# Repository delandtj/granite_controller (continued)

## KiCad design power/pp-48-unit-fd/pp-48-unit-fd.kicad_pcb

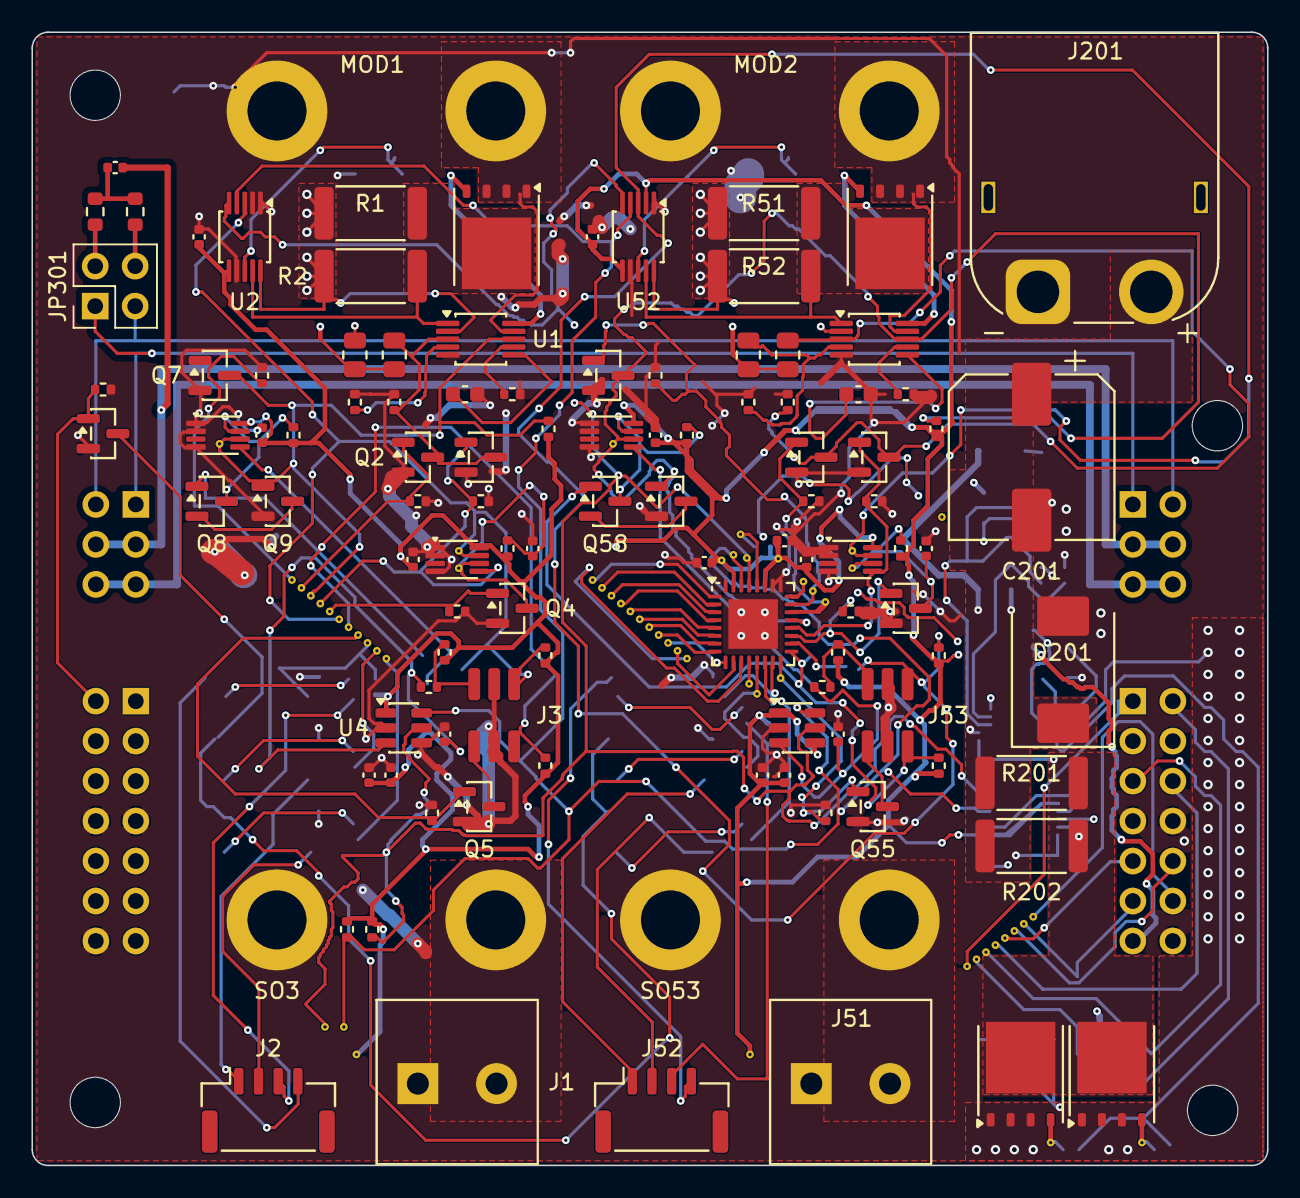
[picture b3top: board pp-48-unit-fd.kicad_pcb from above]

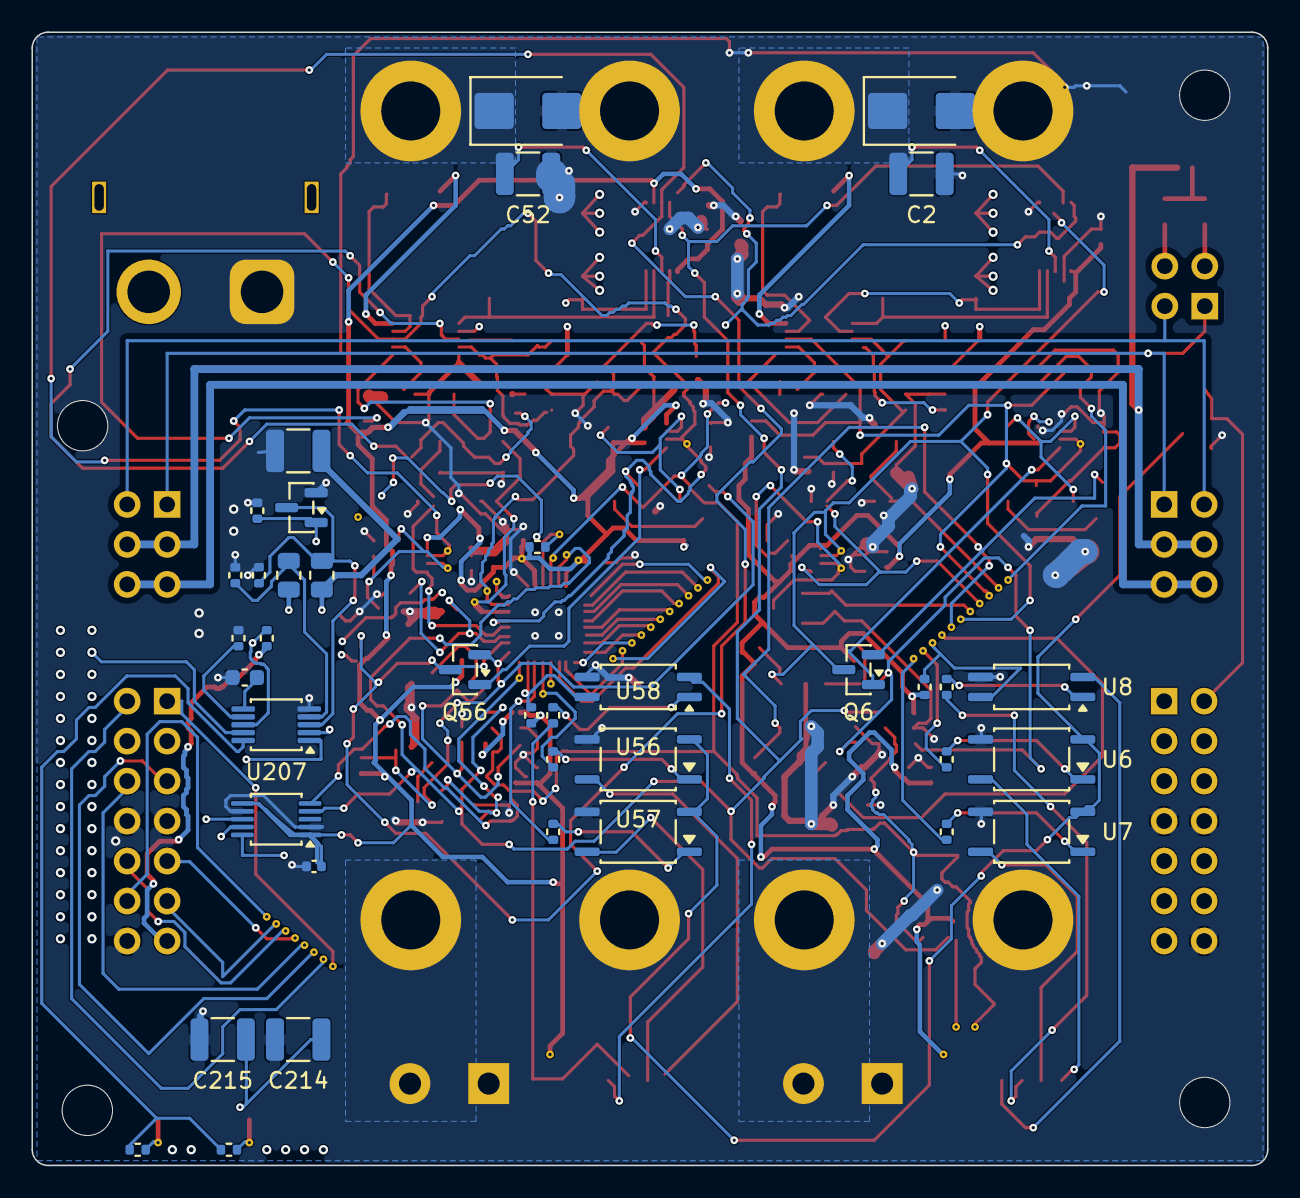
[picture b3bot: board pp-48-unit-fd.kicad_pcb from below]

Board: 4 copper layers, 78.5 x 72.0 mm, 214 parts (42 on the bottom side), 98 nets.

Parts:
BV100, BV101, BV102, BV103, BV104, BV105, BV106, BV107, BV108, BV109, BV110, BV150, BV151, BV152, BV153, BV154, BV155, BV156, BV157, BV158, BV159, BV160, BV900, BV901, BV902, BV903, BV904, BV905, BV906, BV907: (no value)
C1, C51: 100n; C_0603_1608Metric
C2, C52, C202, C214, C215: 2.2u 100V; C_1210_3225Metric
C3, C4, C5, C6, C9, C10, C12, C13, C53, C54, C55, C56, C60, C62, C216: 100n; C_0402_1005Metric
C11, C61: 1u; C_0402_1005Metric
C201: 47u 100V; CP_Elec_10x10
C203: 220n; C_0603_1608Metric
C301: 4.7n; C_0402_1005Metric
D1, D51: SMBJ60A; D_SMB
D201: SMDJ60A; D_SMC
EV12, EV13, EV16, EV22, EV23, EV24, EV29, EV30: (no value)
GV202, GV203: (no value)
H1, H2, H3, H4: MountingHole_3.2mm_M3
J1, J51: NODE 19V; TerminalBlock_Degson_DG128-5.0-02P
J2, J52: FRONT PANEL; JST_GH_SM04B-GHS-TB_1x04-1MP_P1.25mm_Horizontal
J3, J53: AUX; PM_Aux_Socket_2x03_P1.27
J201: XT60PW-M; AMASS_XT60PW-M_1x02_P7.20mm_Horizontal
J301: CHAIN IN; PinHeader_2x07_P2.54mm_Horizontal
J302: CHAIN OUT; PinSocket_2x07_P2.54mm_Horizontal
J303: LINK IN; PinHeader_2x03_P2.54mm_Horizontal
J304: LINK OUT; PinSocket_2x03_P2.54mm_Horizontal
JP301: TERM; PinHeader_2x02_P2.54mm_Vertical
MOD1, MOD2: PM_Module_Outline
PV1B3, PV1B4, PV3A, PV3B: (no value)
Q1, Q51: CSD19532Q5B; TDSON-8-1
Q2, Q3, Q4, Q5, Q6, Q7, Q8, Q9, Q10, Q52, Q53, Q54, Q55, Q56, Q57, Q58, Q59, Q204: 2N7002; SOT-23
Q202, Q203: BSC040N10NS5; TDSON-8-1
R1, R2, R51, R52: 7m 2W; R_2512_6332Metric
R3, R53, R233: 143k; R_0805_2012Metric
R4, R54, R234: 11k; R_0402_1005Metric
R5, R55, R235: 124k; R_0805_2012Metric
R6, R56, R236: 4.99k; R_0402_1005Metric
R7, R57: 13.7k; R_0402_1005Metric
R8, R13, R14, R15, R30, R58, R63, R64, R65, R238: 10k; R_0402_1005Metric
R9, R10, R11, R12, R23, R28, R29, R31, R59, R60, R61, R62, R73, R78, R79, R214: 100k; R_0402_1005Metric
R19, R20, R69, R70: 270; R_0402_1005Metric
R21, R71: 220; R_0402_1005Metric
R22, R72: 47k; R_0402_1005Metric
R24, R74: 1k; R_0402_1005Metric
R26, R27: 4.7k; R_0402_1005Metric
R201, R202: 6m 2W; R_2512_6332Metric
R210, R211: 10; R_0402_1005Metric
R237: 20.0k; R_0402_1005Metric
R301, R302: 60.4; R_0603_1608Metric
RV1: (no value)
SO1, SO51: S1 VIN; PM_Standoff_M2x7_SMTSO
SO2, SO52: S2 GND; PM_Standoff_M2x7_SMTSO
SO3, SO53: S3 GND; PM_Standoff_M2x7_SMTSO
SO4, SO54: S4 VOUT; PM_Standoff_M2x7_SMTSO
SV8, SV9: (no value)
U1, U51, U207: LM5069MM-2; MSOP-10_3x3mm_P0.5mm
U2, U52, U208: INA228AIDGSR; TSSOP-10_3x3mm_P0.5mm
U3, U10, U53, U60: 74LVC1G74; VSSOP-8_2.3x2mm_P0.5mm
U4, U54: ADC121C027CIMK; TSOT-23-6
U5: TCA6424ARGJR; VQFN-32-1EP_5x5mm_P0.5mm_EP3.15x3.15mm
U6, U7, U56, U57: TLP176AM; SOIC-4_4.55x3.7mm_P2.54mm
U8, U58: TLP291; SOIC-4_4.55x2.6mm_P1.27mm
UV1: (no value)
XV1A1, XV1A2, XV1A3, XV1B1, XV1B2, XV1B3: (no value)

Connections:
+3V3: C3.1, C4.1, C9.1, C10.1, C11.1, C12.1, C13.1, C53.1, C54.1, C60.1, C61.1, C62.1, C216.1, J301.13, J302.13, PV1B3.1, PV1B4.1, PV3A.1, PV3B.1, R8.1, R11.1, R13.1, R14.1, R15.1, R22.1, R26.1, R27.1, R28.1, R30.2, R58.1, R61.1, R63.1, R64.1, R65.1, R72.1, R78.1, R238.1, U2.6, U3.8, U4.1, U5.27, U5.31, U10.8, U52.2, U52.6, U53.8, U54.1, U54.4, U60.8, U208.1, U208.6
/Chain/AUX_12V: J303.5, J303.6, J304.5, J304.6
/Chain/CAN_N: J303.2, J304.2, JP301.3
/Chain/CAN_P: J303.1, J304.1, JP301.1
/Chain/CH1_SCL: BV907.1, J301.10, J302.12
/Chain/CH1_SDA: BV906.1, J301.9, J302.11
/Chain/CH2_SCL: BV905.1, J301.6, J302.10
/Chain/CH2_SDA: BV904.1, J301.5, J302.9
/Chain/CH3_SCL: BV903.1, J301.4, J302.6
/Chain/CH3_SDA: BV902.1, J301.3, J302.5
/Chain/LINK_GND: C301.2, J303.3, J303.4, J304.3, J304.4
/Chain/TERM_H: JP301.2, R301.1
/Chain/TERM_L: JP301.4, R302.2
/Chain/TERM_MID: C301.1, R301.2, R302.1
/EXP_RSTN: BV900.1, J301.1, J302.1, R30.1, RV1.1, U5.28
/Input/GATE: R210.1, R211.2, U207.10
/Input/OVLO: R235.2, R236.1, U207.4
/Input/PWR: R237.1, U207.7
/Input/TIMER: C203.1, U207.6
/Input/USENSE: Q202.5, Q203.5, R201.2, R202.2, U207.1, U208.9
/Input/UVLO: Q204.3, R233.2, R234.1, U207.3
/PRESS_EN: BV901.1, J301.2, J302.2, Q10.1, R31.1
/SEG_SCL: EV29.1, J301.12, R27.2, SV9.1, U2.5, U4.5, U5.29, U52.5, U54.5, U208.5
/SEG_SDA: EV30.1, J301.11, R26.2, SV8.1, U2.4, U4.6, U5.30, U52.4, U54.6, U208.4
/U_OFF: EV12.1, Q204.1, R214.1, U5.12, UV1.1
/U_PGD: EV24.1, R238.2, U5.24, U207.8
/Unit/A_ARM: Q6.1, U10.5
/Unit/A_ARMS_M: Q8.2, Q9.3
/Unit/A_ARMS_N: Q8.3, R28.2, U10.7
/Unit/A_CLRN: C5.1, Q4.3, R11.2, U3.6, XV1A2.1
/Unit/A_DISARM: BV100.1, BV150.1, Q7.1, R29.1, U5.1
/Unit/A_GATE: Q1.4, U1.10
/Unit/A_ID: J3.3, R15.2, R24.2
/Unit/A_ID_F: C6.1, R24.1, U4.3
/Unit/A_LCLR: BV104.1, BV154.1, Q4.1, R12.1, U5.5
/Unit/A_LED: BV108.1, BV158.1, R22.2, U5.9, U8.4
/Unit/A_LQ: BV103.1, BV153.1, Q3.1, R10.1, U3.5, U5.4
/Unit/A_NODE: J1.2, SO4.1
/Unit/A_OFF: BV101.1, BV151.1, Q2.1, R9.1, U5.2
/Unit/A_OUT: C2.1, D1.1, Q1.1, Q1.2, Q1.3, SO1.1, U1.9, U2.8
/Unit/A_OVK: BV105.1, BV155.1, J3.1, Q6.3, R13.2, U2.3, U3.7, U5.6, XV1A1.1
/Unit/A_OVLO: R5.2, R6.1, U1.4
/Unit/A_PG: BV106.1, BV156.1, J3.2, Q6.2, Q8.1, R14.2, U5.7
/Unit/A_PGD: BV102.1, BV152.1, Q7.3, Q9.1, R8.2, U1.8, U5.3, U10.6, XV1A3.1
/Unit/A_PLED_A: R21.2, U8.1
/Unit/A_PLED_N: J2.4, U8.2
/Unit/A_PLED_P: J2.3, R21.1
/Unit/A_PWR: R7.1, U1.7
/Unit/A_PWRD: BV109.1, BV159.1, R19.1, U5.10
/Unit/A_PWRD_A: R19.2, U6.1
/Unit/A_PWR_SW: J2.1, U6.6
/Unit/A_RSTD: BV110.1, BV160.1, R20.1, U5.11
/Unit/A_RSTD_A: R20.2, U7.1
/Unit/A_RST_SW: J2.2, U7.6
/Unit/A_RUN: J3.4, Q5.3
/Unit/A_RUNOFF: BV107.1, BV157.1, Q5.1, R23.1, U5.8
/Unit/A_SENSE: Q1.5, R1.2, R2.2, U1.1, U2.9
/Unit/A_TIMER: C1.1, U1.6
/Unit/A_UVLO: Q2.3, Q3.3, R3.2, R4.1, U1.3
/Unit/B_ARM: Q56.1, U60.5
/Unit/B_ARMS_M: Q58.2, Q59.3
/Unit/B_ARMS_N: Q58.3, R78.2, U60.7
/Unit/B_CLRN: C55.1, Q54.3, R61.2, U53.6, XV1B2.1
/Unit/B_DISARM: EV23.1, Q57.1, R79.1, U5.23
/Unit/B_GATE: Q51.4, U51.10
/Unit/B_ID: J53.3, R65.2, R74.2
/Unit/B_ID_F: C56.1, R74.1, U54.3
/Unit/B_LCLR: Q54.1, R62.1, U5.19
/Unit/B_LED: R72.2, U5.15, U58.4
/Unit/B_LQ: Q53.1, R60.1, U5.20, U53.5
/Unit/B_NODE: J51.2, SO54.1
/Unit/B_OFF: EV22.1, Q52.1, R59.1, U5.22
/Unit/B_OUT: C52.1, D51.1, Q51.1, Q51.2, Q51.3, SO51.1, U51.9, U52.8
/Unit/B_OVK: J53.1, Q56.3, R63.2, U5.18, U52.3, U53.7, XV1B1.1
/Unit/B_OVLO: R55.2, R56.1, U51.4
/Unit/B_PG: J53.2, Q56.2, Q58.1, R64.2, U5.17
/Unit/B_PGD: Q57.3, Q59.1, R58.2, U5.21, U51.8, U60.6, XV1B3.1
/Unit/B_PLED_A: R71.2, U58.1
/Unit/B_PLED_N: J52.4, U58.2
/Unit/B_PLED_P: J52.3, R71.1
/Unit/B_PWR: R57.1, U51.7
/Unit/B_PWRD: EV13.1, R69.1, U5.13
/Unit/B_PWRD_A: R69.2, U56.1
/Unit/B_PWR_SW: J52.1, U56.6
/Unit/B_RSTD: R70.1, U5.14
/Unit/B_RSTD_A: R70.2, U57.1
/Unit/B_RST_SW: J52.2, U57.6
/Unit/B_RUN: J53.4, Q55.3
/Unit/B_RUNOFF: EV16.1, Q55.1, R73.1, U5.16
/Unit/B_SENSE: Q51.5, R51.2, R52.2, U51.1, U52.9
/Unit/B_TIMER: C51.1, U51.6
/Unit/B_UVLO: Q52.3, Q53.3, R53.2, R54.1, U51.3
/Unit/PRESS_RTN: Q10.3, U6.3, U7.3, U56.3, U57.3
GND: C1.2, C2.2, C3.2, C4.2, C5.2, C6.2, C9.2, C10.2, C11.2, C12.2, C13.2, C51.2, C52.2, C53.2, C54.2, C55.2, C56.2, C60.2, C61.2, C62.2, C201.2, C202.2, C203.2, C214.2, C215.2, C216.2, D1.2, D51.2, D201.2, J1.1, J3.5, J3.6, J51.1, J53.5, J53.6, J201.1, J301.7, J301.8, J301.14, J302.7, J302.8, J302.14, Q2.2, Q3.2, Q4.2, Q5.2, Q7.2, Q9.2, Q10.2, Q52.2, Q53.2, Q54.2, Q55.2, Q57.2, Q59.2, Q204.2, R4.2, R6.2, R7.2, R9.2, R10.2, R12.2, R23.2, R29.2, R31.2, R54.2, R56.2, R57.2, R59.2, R60.2, R62.2, R73.2, R79.2, R214.2, R234.2, R236.2, R237.2, SO2.1, SO3.1, SO52.1, SO53.1, U1.5, U2.1, U2.2, U2.7, U3.1, U3.2, U3.4, U4.2, U4.4, U5.25, U5.26, U5.33, U6.4, U7.4, U8.3, U10.1, U10.2, U10.4, U51.5, U52.1, U52.7, U53.1, U53.2, U53.4, U54.2, U56.4, U57.4, U58.3, U60.1, U60.2, U60.4, U207.5, U208.2, U208.7
unnamed: GV202.1, Q202.4, R210.2
unnamed: GV203.1, Q203.4, R211.1
VBUS: C214.1, C215.1, Q202.1, Q202.2, Q202.3, Q203.1, Q203.2, Q203.3, R1.1, R2.1, R3.1, R5.1, R51.1, R52.1, R53.1, R55.1, U1.2, U2.10, U51.2, U52.10, U207.9, U208.8
VIN: C201.1, C202.1, D201.1, J201.2, R201.1, R202.1, R233.1, R235.1, U207.2, U208.10

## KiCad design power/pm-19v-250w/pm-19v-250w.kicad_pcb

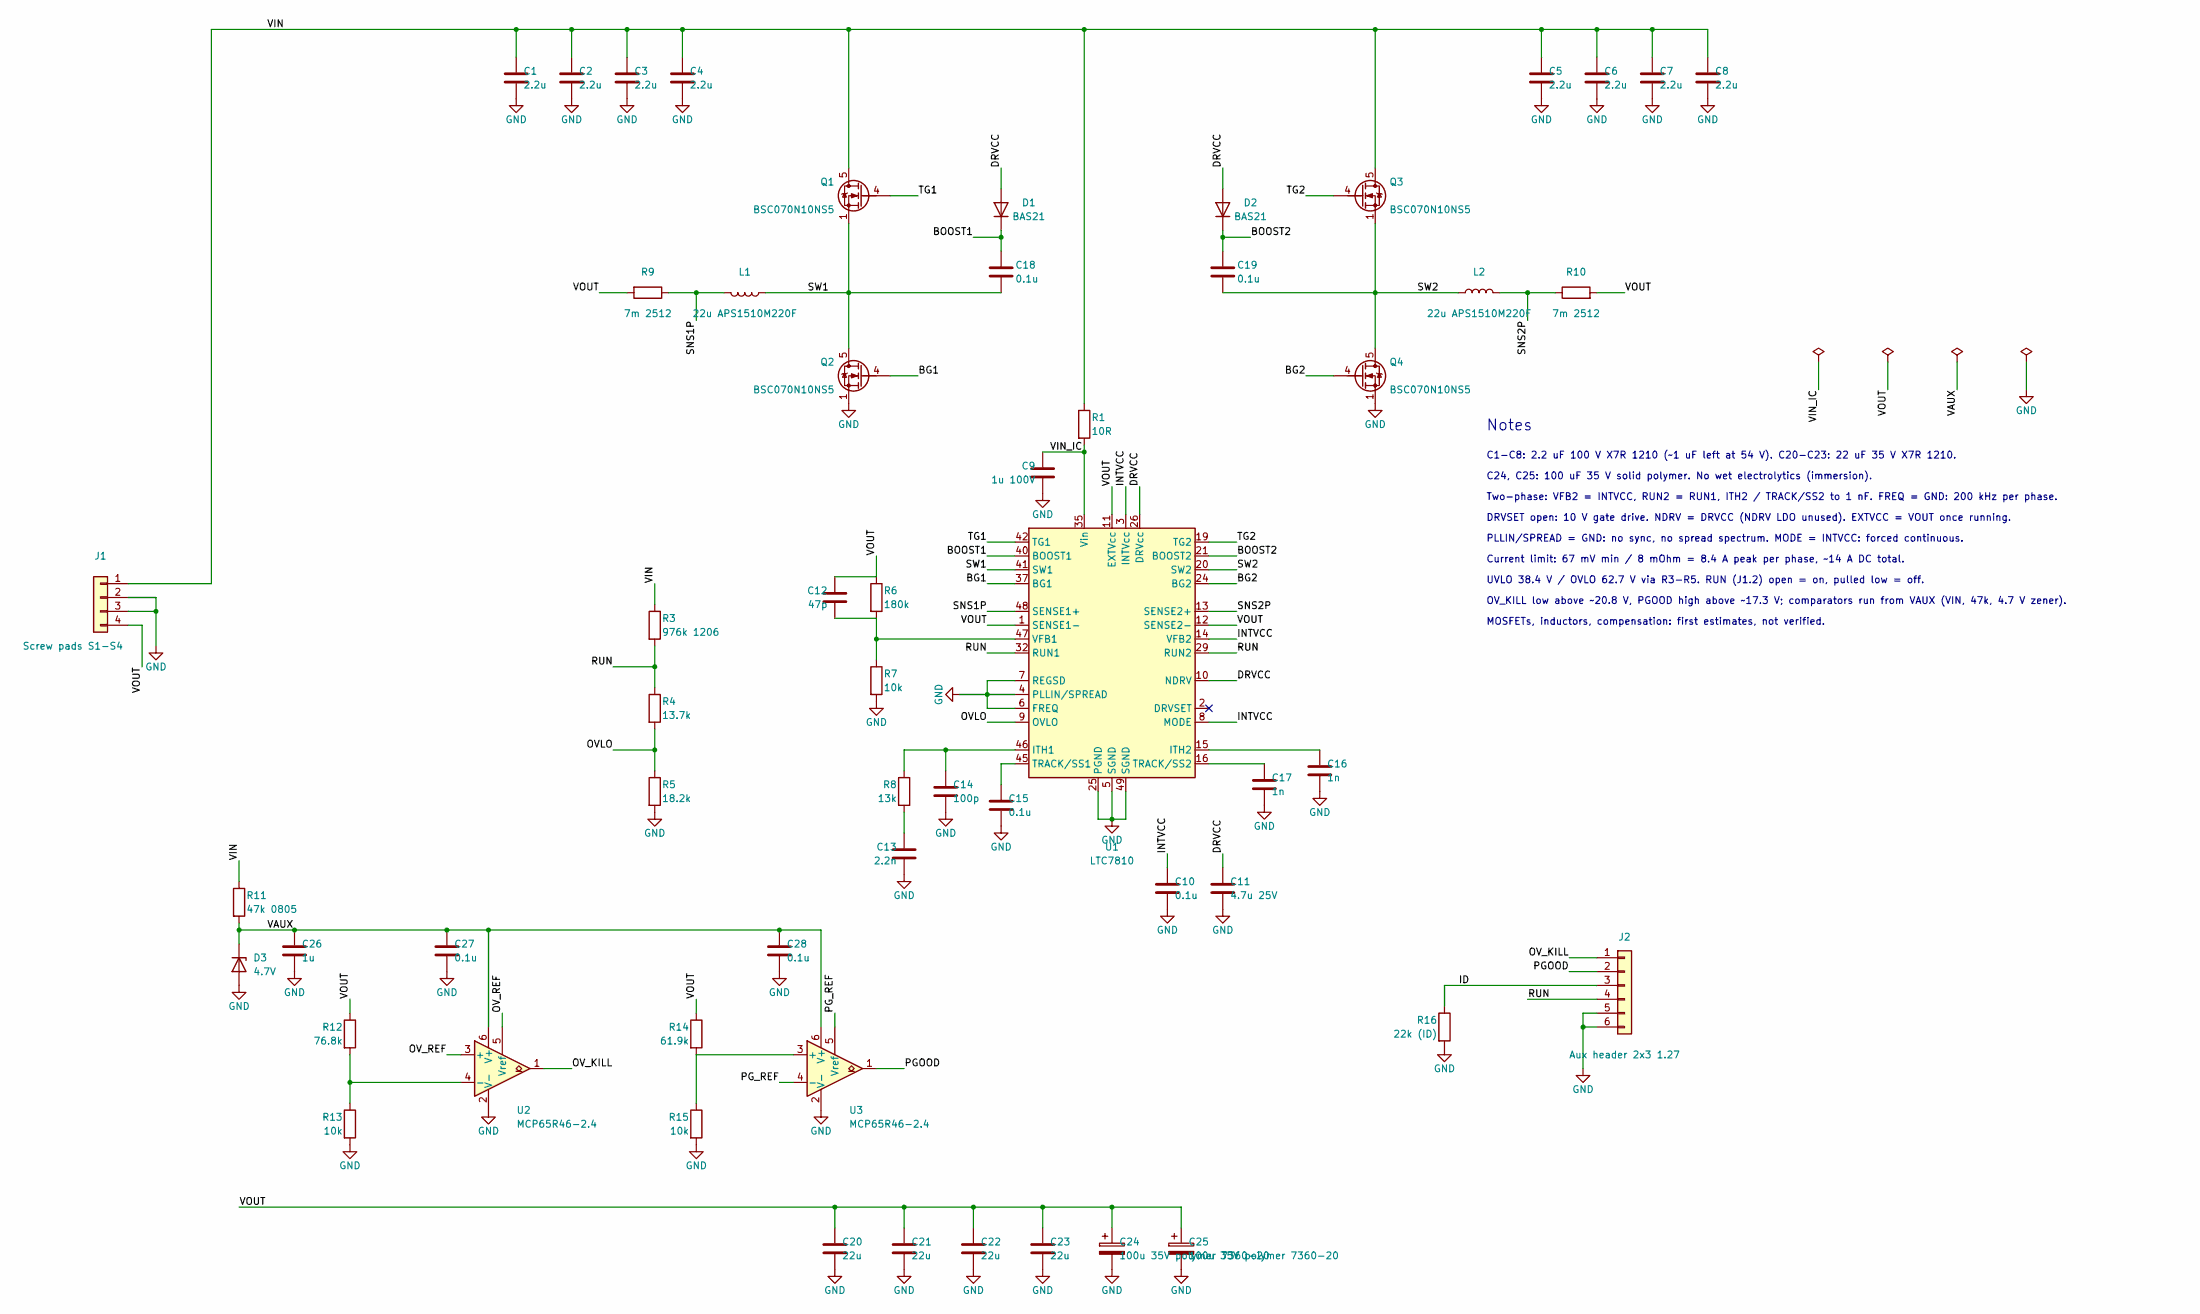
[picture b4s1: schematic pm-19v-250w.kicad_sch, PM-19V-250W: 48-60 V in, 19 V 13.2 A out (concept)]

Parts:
C1, C2, C3, C4, C5, C6, C7, C8: 2.2u; C_1210_3225Metric; LCSC C5449052
C9: 1u 100V; C_0805_2012Metric; LCSC C5370002
C10, C15, C18, C19, C27, C28: 0.1u; C_0402_1005Metric; LCSC C307331
C11: 4.7u 25V; C_0805_2012Metric; LCSC C354262
C12: 47p; C_0402_1005Metric; LCSC C1567
C13: 2.2n; C_0402_1005Metric; LCSC C2980802
C14: 100p; C_0402_1005Metric; LCSC C1546
C16, C17: 1n; C_0402_1005Metric; LCSC C1523
C20, C21, C22, C23: 22u; C_1210_3225Metric; LCSC C778721
C24, C25: 100u 35V polymer 7360-20; CP_EIA-7360-38_Kemet-E; LCSC C2158991
C26: 1u; C_0402_1005Metric; LCSC C52923
D1, D2: BAS21; D_SOD-323; LCSC C82466
D3: 4.7V; D_SOD-323; LCSC C107713
J1: Screw pads S1-S4; PM_Mount_M2
J2: Aux header 2x3 1.27; PM_Aux_Header_2x03_P1.27; LCSC C41376035
L1, L2: 22u APS1510M220F; L_Coilcraft_XAL1510-223; LCSC C49261404
Q1, Q2, Q3, Q4: BSC070N10NS5; TDSON-8-1; LCSC C534364
R1: 10R; R_0603_1608Metric; LCSC C22859
R3: 976k 1206; R_1206_3216Metric; LCSC C247164
R4: 13.7k; R_0603_1608Metric; LCSC C22793
R5: 18.2k; R_0402_1005Metric; LCSC C25859
R6: 180k; R_0402_1005Metric; LCSC C25760
R7, R13, R15: 10k; R_0402_1005Metric; LCSC C25744
R8: 13k; R_0402_1005Metric; LCSC C25754
R9, R10: 7m 2512; R_2512_6332Metric; LCSC C20608751
R11: 47k 0805; R_0805_2012Metric; LCSC C17713
R12: 76.8k; R_0402_1005Metric; LCSC C26987
R14: 61.9k; R_0402_1005Metric; LCSC C2933106
R16: 22k (ID); R_0603_1608Metric; LCSC C31850
U1: LTC7810; LQFP-48-1EP_7x7mm_P0.5mm_EP3.6x3.6mm; LCSC C581067
U2, U3: MCP65R46-2.4; SOT-23-6; LCSC C623510

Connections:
/BG1: Q2.4 (G), U1.37 (BG1)
/BG2: Q4.4 (G), U1.24 (BG2)
/BOOST1: C18.1, D1.1 (K), U1.40 (BOOST1)
/BOOST2: C19.1, D2.1 (K), U1.21 (BOOST2)
/DRVCC: C11.1, D1.2 (A), D2.2 (A), U1.10 (NDRV), U1.26 (DRVcc)
/ID: J2.3, R16.1
/INTVCC: C10.1, U1.3 (INTVcc), U1.8 (MODE), U1.14 (VFB2)
/OVLO: R4.2, R5.1, U1.9 (OVLO)
/OV_KILL: J2.1, U2.1
/OV_REF: U2.3 (+), U2.5 (Vref)
/PGOOD: J2.2, U3.1
/PG_REF: U3.4 (-), U3.5 (Vref)
/RUN: J2.4, R3.2, R4.1, U1.29 (RUN2), U1.32 (RUN1)
/SNS1P: L1.2, R9.1, U1.48 (SENSE1+)
/SNS2P: L2.2, R10.1, U1.13 (SENSE2+)
/SW1: C18.2, L1.1, Q1.1 (S), Q1.2 (S), Q1.3 (S), Q2.5 (D), U1.41 (SW1)
/SW2: C19.2, L2.1, Q3.1 (S), Q3.2 (S), Q3.3 (S), Q4.5 (D), U1.20 (SW2)
/TG1: Q1.4 (G), U1.42 (TG1)
/TG2: Q3.4 (G), U1.19 (TG2)
/VAUX: C26.1, C27.1, C28.1, D3.1 (K), R11.2, U2.6 (V+), U3.6 (V+)
/VIN: C1.1, C2.1, C3.1, C4.1, C5.1, C6.1, C7.1, C8.1, J1.1, Q1.5 (D), Q3.5 (D), R1.1, R3.1, R11.1
/VIN_IC: C9.1, R1.2, U1.35 (Vin)
/VOUT: C12.1, C20.1, C21.1, C22.1, C23.1, C24.1, C25.1, J1.4, R6.1, R9.2, R10.2, R12.1, R14.1, U1.1 (SENSE1-), U1.11 (EXTVcc), U1.12 (SENSE2-)
GND: C1.2, C2.2, C3.2, C4.2, C5.2, C6.2, C7.2, C8.2, C9.2, C10.2, C11.2, C13.2, C14.2, C15.2, C16.2, C17.2, C20.2, C21.2, C22.2, C23.2, C24.2, C25.2, C26.2, C27.2, C28.2, D3.2 (A), J1.2, J1.3, J2.5, J2.6, Q2.1 (S), Q2.2 (S), Q2.3 (S), Q4.1 (S), Q4.2 (S), Q4.3 (S), R5.2, R7.2, R13.2, R15.2, R16.2, U1.4 (PLLIN/SPREAD), U1.5 (SGND), U1.6 (FREQ), U1.7 (REGSD), U1.25 (PGND), U1.49 (SGND), U2.2 (V-), U3.2 (V-)
unnamed: C13.1, R8.2
unnamed: C14.1, R8.1, U1.46 (ITH1)
unnamed: C16.1, U1.15 (ITH2)
unnamed: C15.1, U1.45 (TRACK/SS1)
unnamed: C17.1, U1.16 (TRACK/SS2)
unnamed: C12.2, R6.2, R7.1, U1.47 (VFB1)
unnamed: R12.2, R13.1, U2.4 (-)
unnamed: R14.2, R15.1, U3.3 (+)

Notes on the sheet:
Notes
C1-C8: 2.2 uF 100 V X7R 1210 (~1 uF left at 54 V). C20-C23: 22 uF 35 V X7R 1210.
C24, C25: 100 uF 35 V solid polymer. No wet electrolytics (immersion).
Two-phase: VFB2 = INTVCC, RUN2 = RUN1, ITH2 / TRACK/SS2 to 1 nF. FREQ = GND: 200 kHz per phase.
DRVSET open: 10 V gate drive. NDRV = DRVCC (NDRV LDO unused). EXTVCC = VOUT once running.
PLLIN/SPREAD = GND: no sync, no spread spectrum. MODE = INTVCC: forced continuous.
Current limit: 67 mV min / 8 mOhm = 8.4 A peak per phase, ~14 A DC total.
UVLO 38.4 V / OVLO 62.7 V via R3-R5. RUN (J1.2) open = on, pulled low = off.
OV_KILL low above ~20.8 V, PGOOD high above ~17.3 V; comparators run from VAUX (VIN, 47k, 4.7 V zener).
MOSFETs, inductors, compensation: first estimates, not verified.

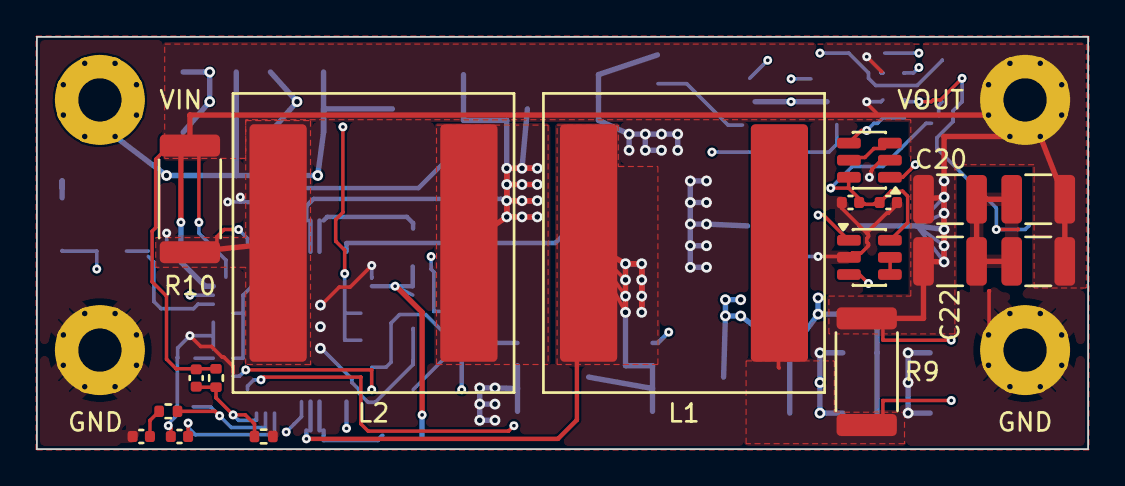
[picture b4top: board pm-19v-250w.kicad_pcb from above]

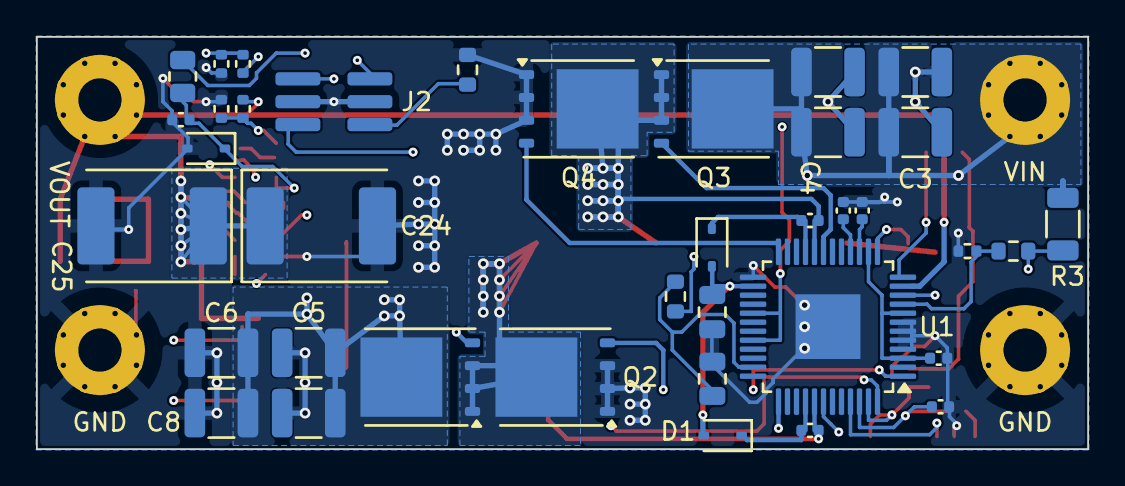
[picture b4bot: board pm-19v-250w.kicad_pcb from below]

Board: 4 copper layers, 58.4 x 22.9 mm, 57 parts (38 on the bottom side), 32 nets.

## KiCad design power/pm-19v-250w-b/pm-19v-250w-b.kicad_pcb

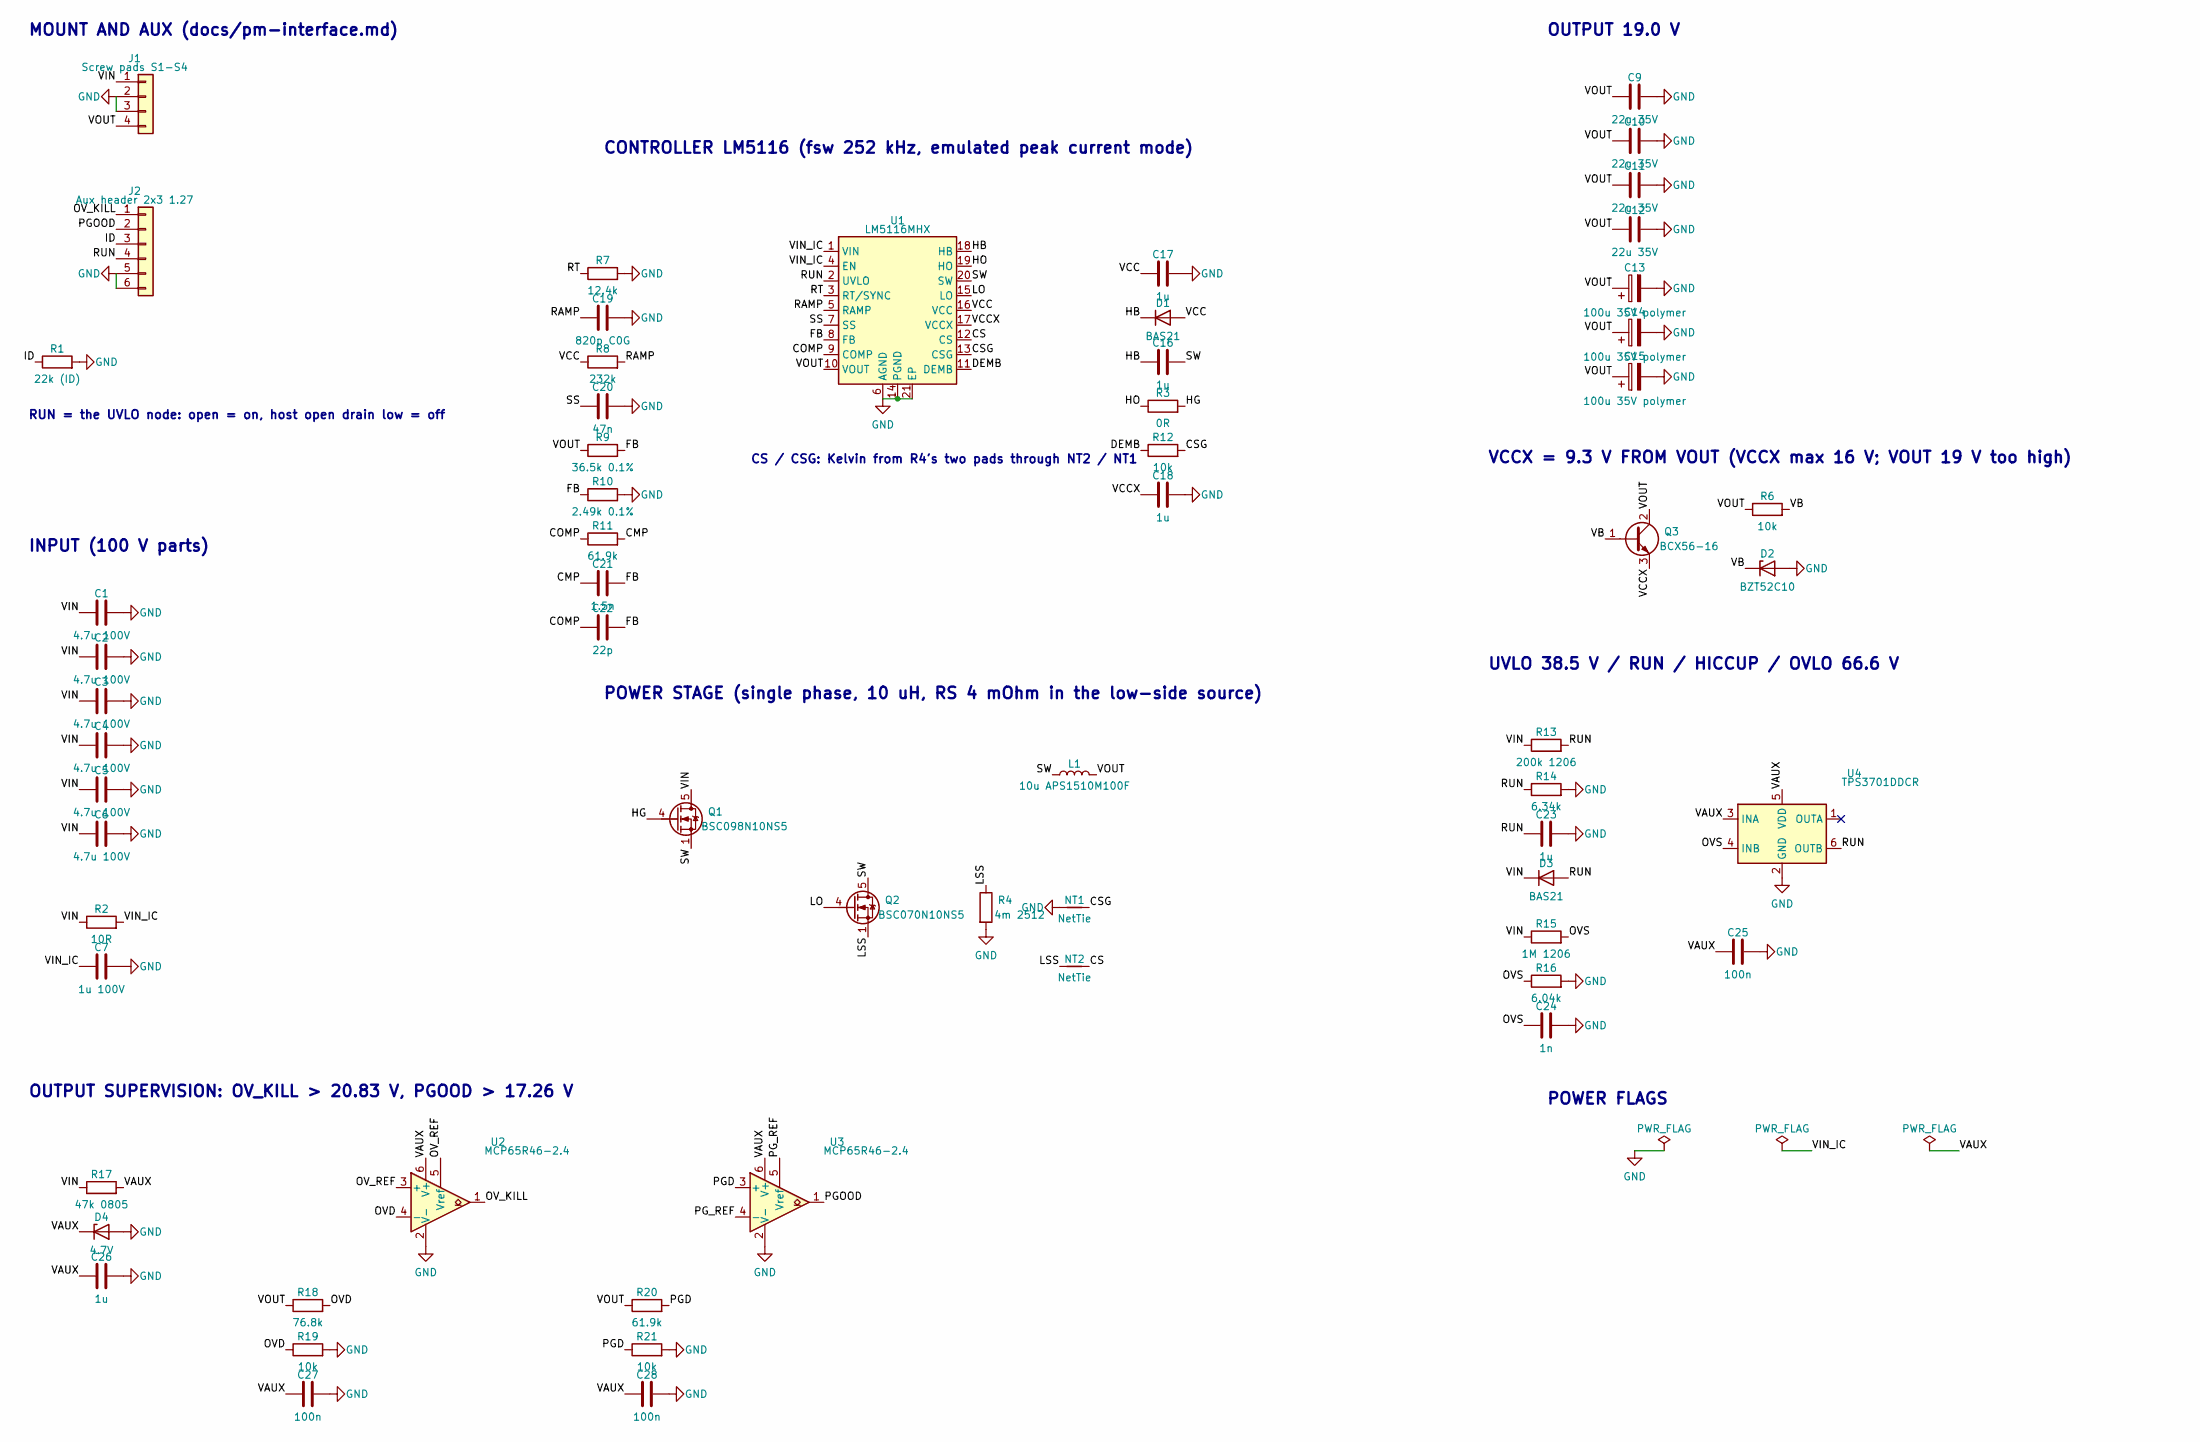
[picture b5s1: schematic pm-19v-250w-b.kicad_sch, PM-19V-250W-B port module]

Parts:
C1, C2, C3, C4, C5, C6: 4.7u 100V; C_1210_3225Metric; LCSC C381466
C7: 1u 100V; C_0805_2012Metric; LCSC C5370002
C9, C10, C11, C12: 22u 35V; C_1210_3225Metric; LCSC C778721
C13, C14, C15: 100u 35V polymer; CP_Elec_6.3x7.7; LCSC C46550467
C16, C17, C18, C23, C26: 1u; C_0402_1005Metric; LCSC C52923
C19: 820p C0G; C_0402_1005Metric; LCSC C161159
C20: 47n; C_0402_1005Metric; LCSC C272875
C21: 1.5n; C_0402_1005Metric; LCSC C107022
C22: 22p; C_0402_1005Metric; LCSC C1555
C24: 1n; C_0402_1005Metric; LCSC C1523
C25, C27, C28: 100n; C_0402_1005Metric; LCSC C307331
D1, D3: BAS21; D_SOD-323; LCSC C82466
D2: BZT52C10; D_SOD-123; LCSC C2103
D4: 4.7V; D_SOD-323; LCSC C107713
J1: Screw pads S1-S4; PM_Mount_M2
J2: Aux header 2x3 1.27; PM_Aux_Header_2x03_P1.27; LCSC C41376035
L1: 10u APS1510M100F; L_Coilcraft_XAL1510-103; LCSC C49261402
NT1, NT2: NetTie; NetTie-2_SMD_Pad0.5mm
Q1: BSC098N10NS5; TDSON-8-1; LCSC C534398
Q2: BSC070N10NS5; TDSON-8-1; LCSC C534364
Q3: BCX56-16; SOT-89-3; LCSC C123402
R1: 22k (ID); R_0603_1608Metric; LCSC C31850
R2: 10R; R_0603_1608Metric; LCSC C22859
R3: 0R; R_0402_1005Metric; LCSC C17168
R4: 4m 2512; R_2512_6332Metric; LCSC C459681
R6, R12, R19, R21: 10k; R_0402_1005Metric; LCSC C25744
R7: 12.4k; R_0402_1005Metric; LCSC C2929935
R8: 232k; R_0402_1005Metric; LCSC C3013159
R9: 36.5k 0.1%; R_0402_1005Metric; LCSC C852741
R10: 2.49k 0.1%; R_0402_1005Metric; LCSC C852700
R11, R20: 61.9k; R_0402_1005Metric; LCSC C2933106
R13: 200k 1206; R_1206_3216Metric; LCSC C17954
R14: 6.34k; R_0402_1005Metric; LCSC C5713274
R15: 1M 1206; R_1206_3216Metric; LCSC C17927
R16: 6.04k; R_0402_1005Metric; LCSC C2998182
R17: 47k 0805; R_0805_2012Metric; LCSC C17713
R18: 76.8k; R_0402_1005Metric; LCSC C26987
U1: LM5116MHX; HTSSOP-20-1EP_4.4x6.5mm_P0.65mm_EP3.4x6.5mm_ThermalVias; LCSC C13755
U2, U3: MCP65R46-2.4; SOT-23-6; LCSC C623510
U4: TPS3701DDCR; SOT-23-6; LCSC C132788

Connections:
/CMP: C21.1, R11.2
/COMP: C22.1, R11.1, U1.9 (COMP)
/CS: NT2.2, U1.12 (CS)
/CSG: NT1.2, R12.2, U1.13 (CSG)
/DEMB: R12.1, U1.11 (DEMB)
/FB: C21.2, C22.2, R9.2, R10.1, U1.8 (FB)
/HB: C16.1, D1.1 (K), U1.18 (HB)
/HG: Q1.4 (G), R3.2
/HO: R3.1, U1.19 (HO)
/ID: J2.3, R1.1
/LO: Q2.4 (G), U1.15 (LO)
/LSS: NT2.1, Q2.1 (S), Q2.2 (S), Q2.3 (S), R4.1
/OVD: R18.2, R19.1, U2.4 (-)
/OVS: C24.1, R15.2, R16.1, U4.4 (INB)
/OV_KILL: J2.1, U2.1
/OV_REF: U2.3 (+), U2.5 (Vref)
/PGD: R20.2, R21.1, U3.3 (+)
/PGOOD: J2.2, U3.1
/PG_REF: U3.4 (-), U3.5 (Vref)
/RAMP: C19.1, R8.2, U1.5 (RAMP)
/RT: R7.1, U1.3 (RT/SYNC)
/RUN: C23.1, D3.2 (A), J2.4, R13.2, R14.1, U1.2 (UVLO), U4.6 (OUTB)
/SS: C20.1, U1.7 (SS)
/SW: C16.2, L1.1, Q1.1 (S), Q1.2 (S), Q1.3 (S), Q2.5 (D), U1.20 (SW)
/VAUX: C25.1, C26.1, C27.1, C28.1, D4.1 (K), R17.2, U2.6 (V+), U3.6 (V+), U4.3 (INA), U4.5 (VDD)
/VB: D2.1 (K), Q3.1 (B), R6.2
/VCC: C17.1, D1.2 (A), R8.1, U1.16 (VCC)
/VCCX: C18.1, Q3.3 (E), U1.17 (VCCX)
/VIN: C1.1, C2.1, C3.1, C4.1, C5.1, C6.1, D3.1 (K), J1.1, Q1.5 (D), R2.1, R13.1, R15.1, R17.1
/VIN_IC: C7.1, R2.2, U1.1 (VIN), U1.4 (EN)
/VOUT: C9.1, C10.1, C11.1, C12.1, C13.1, C14.1, C15.1, J1.4, L1.2, Q3.2 (C), R6.1, R9.1, R18.1, R20.1, U1.10 (VOUT)
GND: C1.2, C2.2, C3.2, C4.2, C5.2, C6.2, C7.2, C9.2, C10.2, C11.2, C12.2, C13.2, C14.2, C15.2, C17.2, C18.2, C19.2, C20.2, C23.2, C24.2, C25.2, C26.2, C27.2, C28.2, D2.2 (A), D4.2 (A), J1.2, J1.3, J2.5, J2.6, NT1.1, R1.2, R4.2, R7.2, R10.2, R14.2, R16.2, R19.2, R21.2, U1.6 (AGND), U1.14 (PGND), U1.21 (EP), U2.2 (V-), U3.2 (V-), U4.2 (GND)

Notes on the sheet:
MOUNT AND AUX (docs/pm-interface.md)
RUN = the UVLO node: open = on, host open drain low = off
INPUT (100 V parts)
CONTROLLER LM5116 (fsw 252 kHz, emulated peak current mode)
CS / CSG: Kelvin from R4's two pads through NT2 / NT1
POWER STAGE (single phase, 10 uH, RS 4 mOhm in the low-side source)
OUTPUT 19.0 V
VCCX = 9.3 V FROM VOUT (VCCX max 16 V; VOUT 19 V too high)
UVLO 38.5 V / RUN / HICCUP / OVLO 66.6 V
OUTPUT SUPERVISION: OV_KILL > 20.83 V, PGOOD > 17.26 V
POWER FLAGS

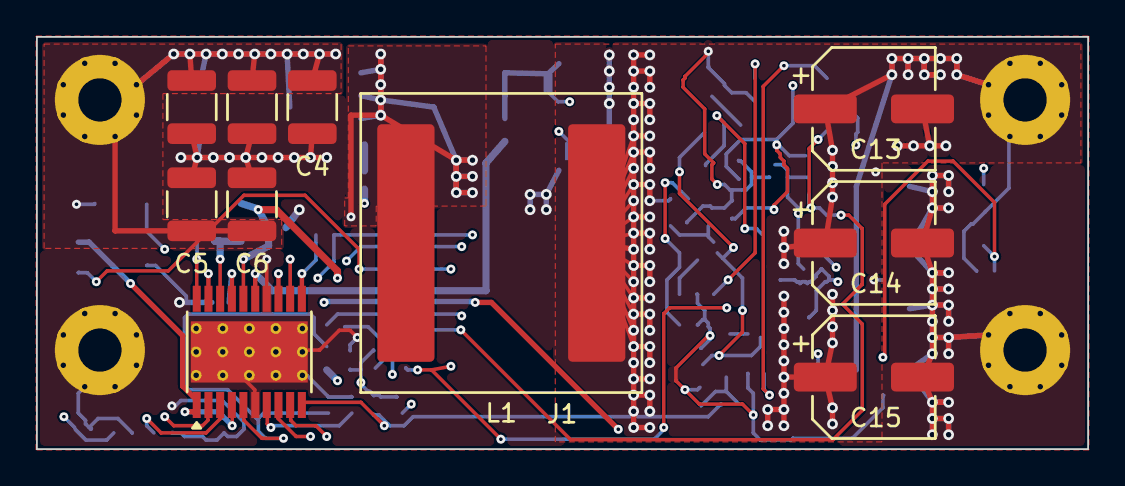
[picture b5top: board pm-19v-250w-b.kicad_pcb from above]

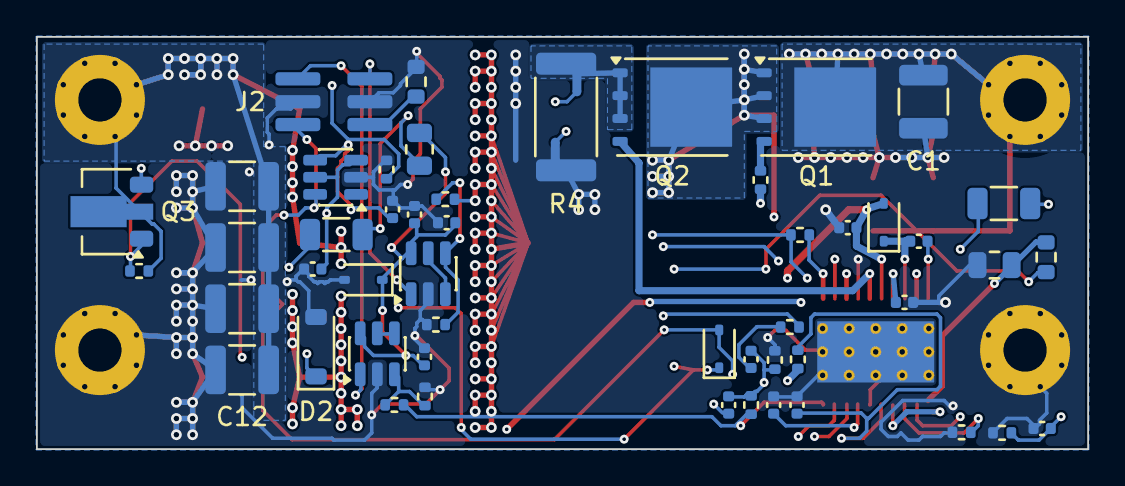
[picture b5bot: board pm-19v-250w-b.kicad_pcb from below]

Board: 4 copper layers, 58.4 x 22.9 mm, 63 parts (52 on the bottom side), 32 nets.
